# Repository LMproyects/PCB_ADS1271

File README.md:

# Diseño PCB de prueba para ADS1271

## Diseñadores
* Luciano Villarreal
* Marcos Postemsky

## Elección de pines

## Modo de operación
Vamos a trabajar con comunicación SPI, adquiriendo datos de forma continua (SYNC-PDWN='1')

## Pines a PinMod

**Para trabajar con SPI**
* **CLK:** reloj continuo que utiliza el ADC para muestreo y conversión.
* **SCLK:** Reloj utilizado para la comunicación SPI.
* **DOUT:** Datos de salida SPI.
* **DRDY:** Una vez que los datos válidos están listos, DRDY se pone en bajo.

### Pines ADS1271 fijos
* **SYNC/PDWN:** Se mantiene este valor en alto, para poder trabajar con adquisición de datos de manera continua. 

## Componentes necesarios
- 1 ADS1271: ADC de 24 bits Delta&Sigma con entrada y referencia diferencial.
- 6 pines con curva de 90º.
- 1 LM7805
- 1 Capacitor electrolítico 0.33 uF, 25V.
- 2 Capacitores electrolítico 0.1 uF
- 2 Capacitores electrolítico 10 uF
- 2 Capacitores cerámica 100 pF
- 1 Capacitores cerámica 1 nF
- 5 Resistencias de 50 Ohmios
- 1 Resistencia de 680 Ohmios
- 1 LM336z2.5 (se puede cambiar por zener de 2.5 v)
- 2 pines 2.54 mm
- 2 pines 2.54 mm

## Diseño del esquematico
Para el diseño del esquemático que será utilizado en el PCB de prueba, se tiene en cuenta el circuito recomendado por el fabricante Texas Instruments. A continuación, puede verse el circuito mencionado.

## Circuitos de entrada

Para la entrada diferencial, el fabricante recomienda dos configuraciones dependiendo el modo en el que se quiera utilizar el ADC.

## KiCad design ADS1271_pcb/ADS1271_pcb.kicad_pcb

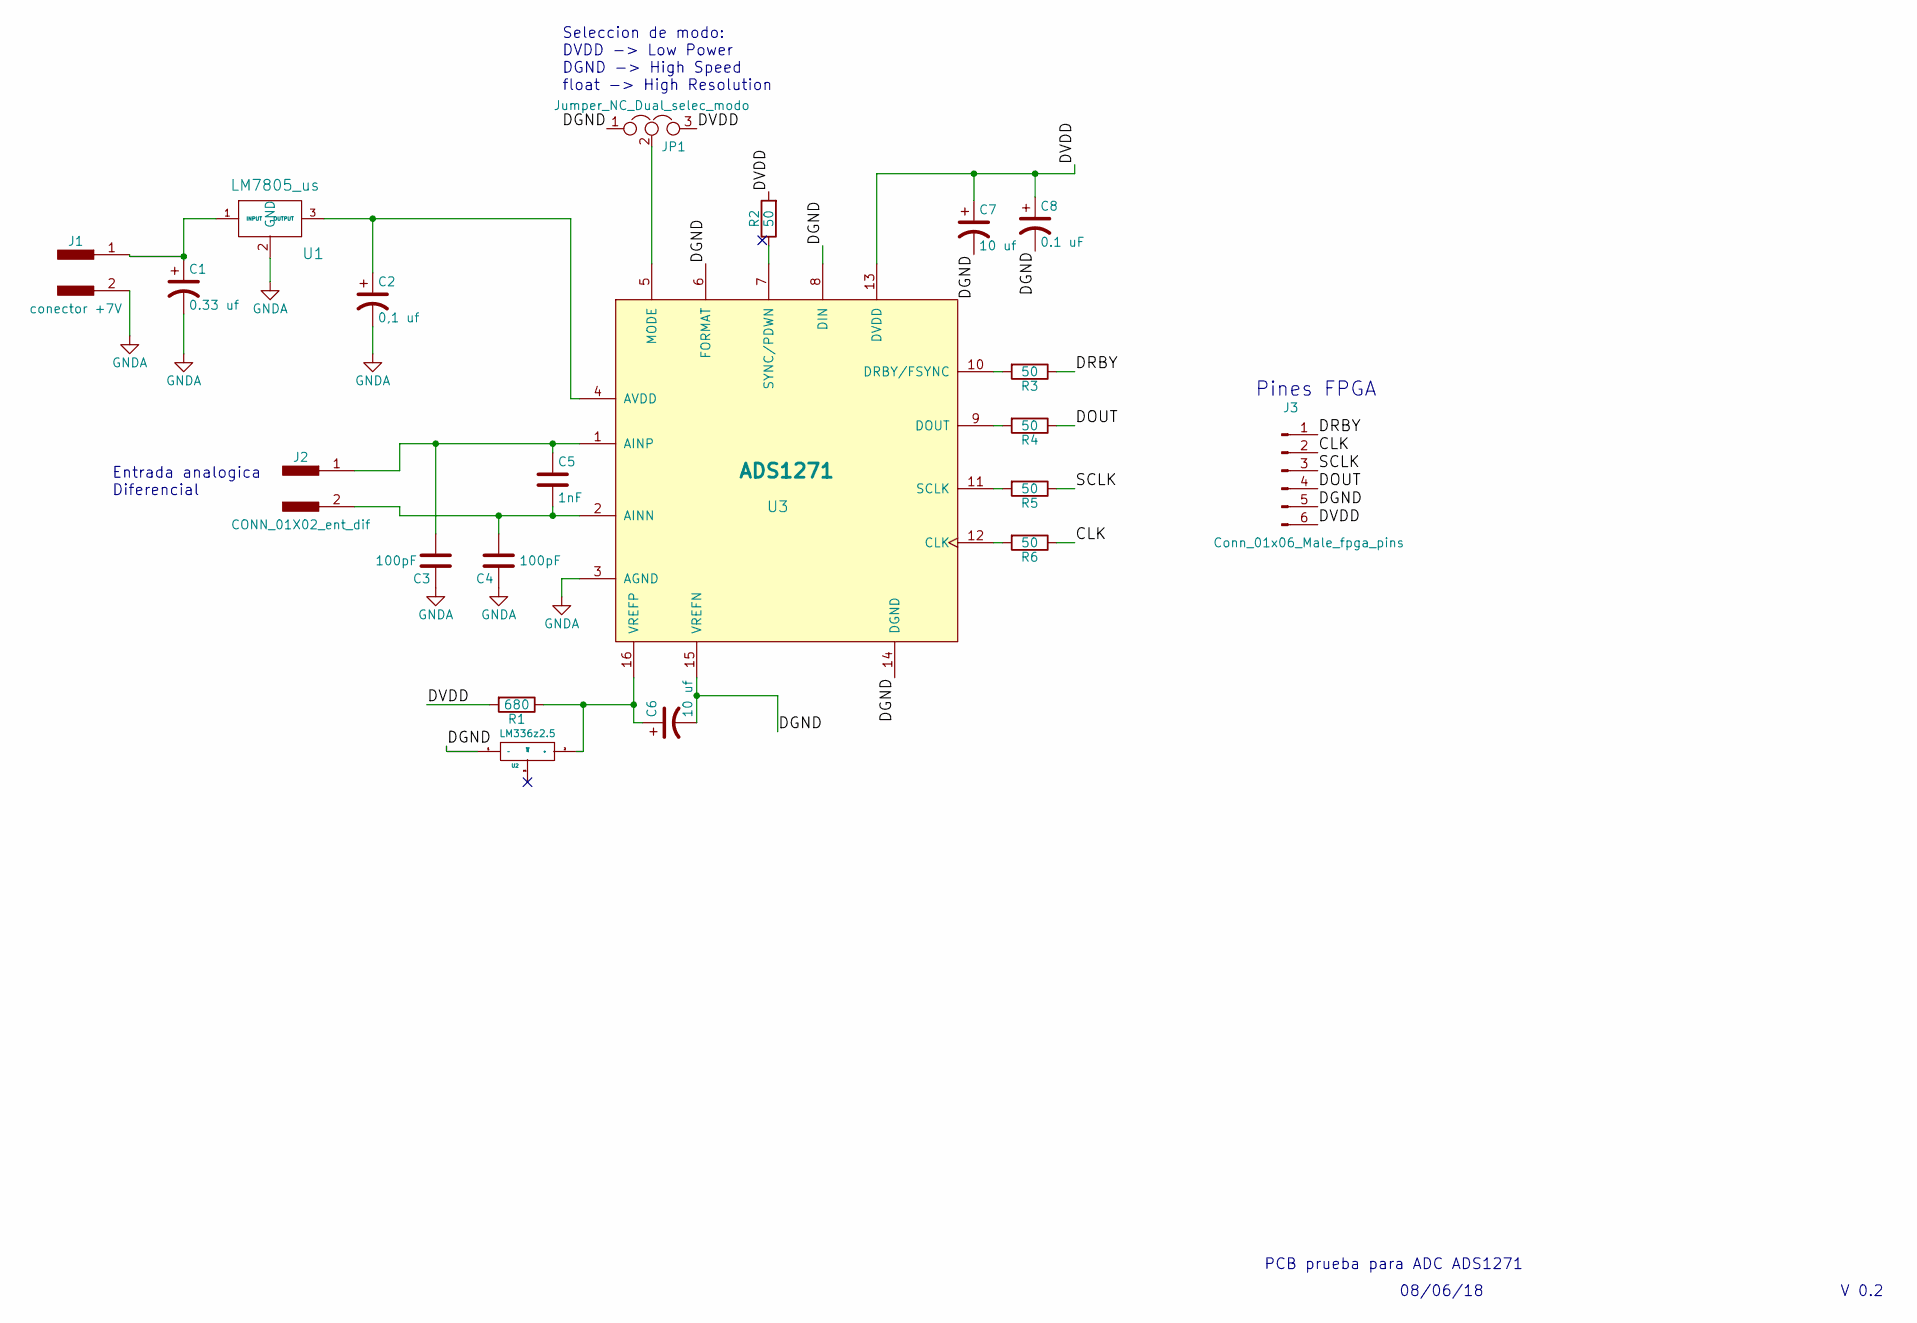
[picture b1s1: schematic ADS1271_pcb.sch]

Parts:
C1: 0.33 uf; CP_Radial_D5.0mm_P2.50mm
C2: 0,1 uf; CP_Radial_D5.0mm_P2.50mm
C3, C4: 100pF; C_Disc_D5.0mm_W2.5mm_P5.00mm
C5: 1nF; C_Disc_D5.0mm_W2.5mm_P5.00mm
C6, C7: 10 uf; CP_Radial_D5.0mm_P2.50mm
C8: 0.1 uF; CP_Radial_D5.0mm_P2.50mm
J1: conector +7V; Molex_SPOX-5267_22-03-5025_02x2.54mm_Straight
J2: CONN_01X02_ent_dif; Molex_SPOX-5267_22-03-5025_02x2.54mm_Straight
J3: Conn_01x06_Male_fpga_pins; Molex_SPOX-5267_22-03-5065_06x2.54mm_Straight
JP1: Jumper_NC_Dual_selec_modo; Molex_SPOX-5267_22-03-5035_03x2.54mm_Straight
R1: 680; R_Axial_DIN0207_L6.3mm_D2.5mm_P5.08mm_Vertical
R2, R3, R4, R5, R6: 50; R_Axial_DIN0207_L6.3mm_D2.5mm_P5.08mm_Vertical
U1: LM7805_us; TO-220-3_Vertical
U2: LM336z2.5; TO-92_Inline_Narrow_Oval
U3: ADS1271; TSSOP-16_4.4x5mm_Pitch0.65mm

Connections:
/CLK: J3.2, R6.1
/DGND: C6.2, C7.2, C8.2, J3.5, JP1.1, U2.1 (-), U3.6 (FORMAT), U3.8 (DIN), U3.14 (DGND), U3.15 (VREFN)
/DOUT: J3.4, R4.1
/DRBY: J3.1, R3.1
/DVDD: C7.1, C8.1, J3.6, JP1.3, R1.2, R2.2, U3.13 (DVDD)
/SCLK: J3.3, R5.1
GNDA: C1.2, C2.2, C3.1, C4.1, J1.2, U1.2 (GND), U3.3 (AGND)
unnamed: C1.1, J1.1, U1.1 (INPUT)
unnamed: C2.1, U1.3 (OUTPUT), U3.4 (AVDD)
unnamed: C3.2, C5.1, J2.1, U3.1 (AINP)
unnamed: C4.2, C5.2, J2.2, U3.2 (AINN)
unnamed: C6.1, R1.1, U2.2 (+), U3.16 (VREFP)
unnamed: JP1.2, U3.5 (MODE)
unnamed: R2.1, U3.7 (SYNC/PDWN)
unnamed: R3.2, U3.10 (DRBY/FSYNC)
unnamed: R4.2, U3.9 (DOUT)
unnamed: R5.2, U3.11 (SCLK)
unnamed: R6.2, U3.12 (CLK)

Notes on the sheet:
Pines FPGA
Entrada analogica Diferencial
Seleccion de modo: DVDD -> Low Power DGND -> High Speed float -> High Resolution
PCB prueba para ADC ADS1271
V 0.2
08/06/18

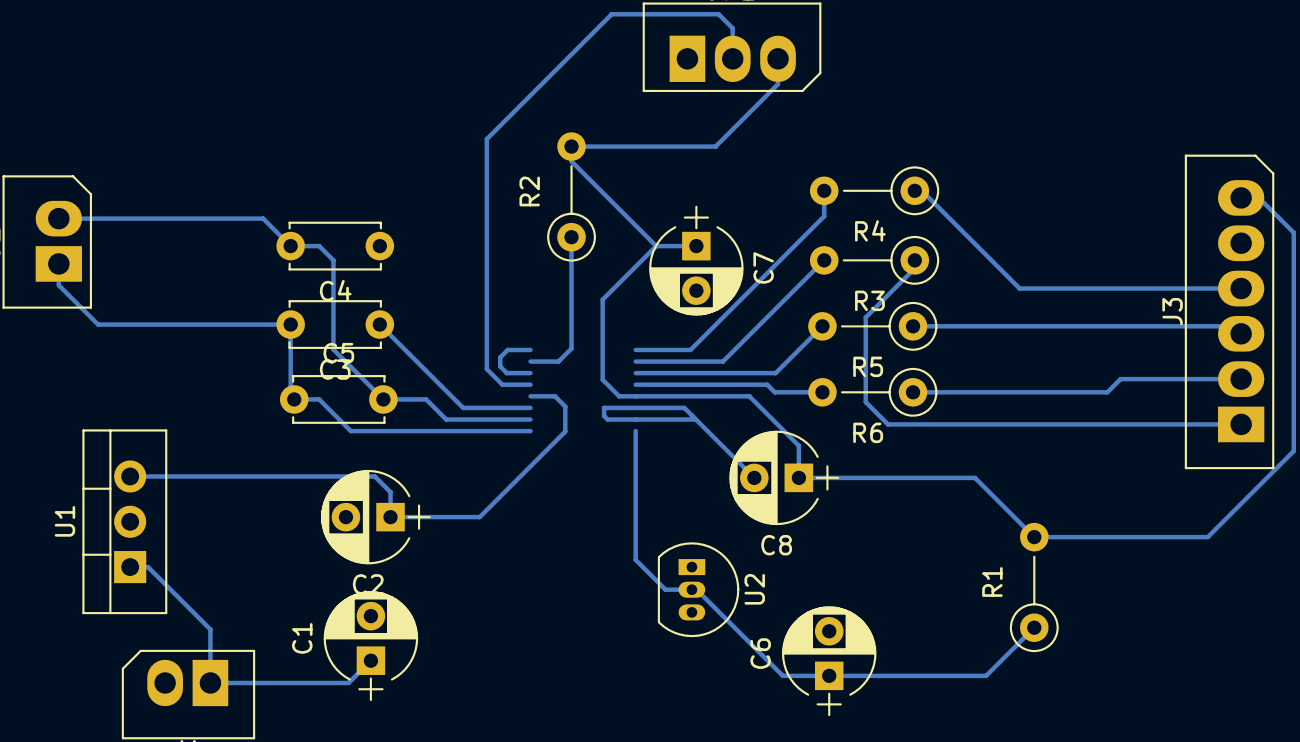
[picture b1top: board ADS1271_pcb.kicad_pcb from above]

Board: 2 copper layers, 21 parts (1 on the bottom side), 18 nets.

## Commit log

2018-06-03 Agrego Readme comienzo pcb
2018-06-03 Creo proyecto kicad
2018-06-05 Se agrega componente ads1271
2018-06-05 Terminé de generar componente ADS1271, faltan detalles finos
2018-06-05 cambios esquematico
2018-06-05 Documentación en README
2018-06-05 Se sume imagen circuito
2018-06-05 Documentacion
2018-06-05 modificacion readme
2018-06-05 Se agrega en el esquematico los labels y resistencias
    FALTA: Capacitores de bypass, baterías, y definir funciones del resto de los pines. @lvillarreal
2018-06-05 Se cambia la conexión de la referencia
2018-06-08 Se completan los componentes basicos, expuestos en datasheet
    Faltaría ver si se coloca filtro de la referencia y filtro para la entrada diferencial.
2018-06-08 Cambios en los capacitores en líneas diferenciales analogicas
2018-07-07 Se listan los componentes
2018-07-07 Se anotan los componentes
2019-02-23 cambio texto en readme
    Solo hago un pequeño cambio en la línea que presenta la figura del circuito recomendado.
2019-02-23 agrego datasheet
2019-02-24 imagen de circuito de entrada
2019-02-24 subolibreria
2019-02-27 PCB Terminado
2019-02-27 Se agrega pdf de la capa de cobre
2019-02-27 Actualizacion de componentes
2019-02-27 Se cambian dos capacitores de ceramica por dos electroliticos, en entrada dvdd (pin 13)
